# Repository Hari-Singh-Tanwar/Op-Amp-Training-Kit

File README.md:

View this project on [CADLAB.io](https://cadlab.io/project/29388). 

# Op-Amp-Training-Kit

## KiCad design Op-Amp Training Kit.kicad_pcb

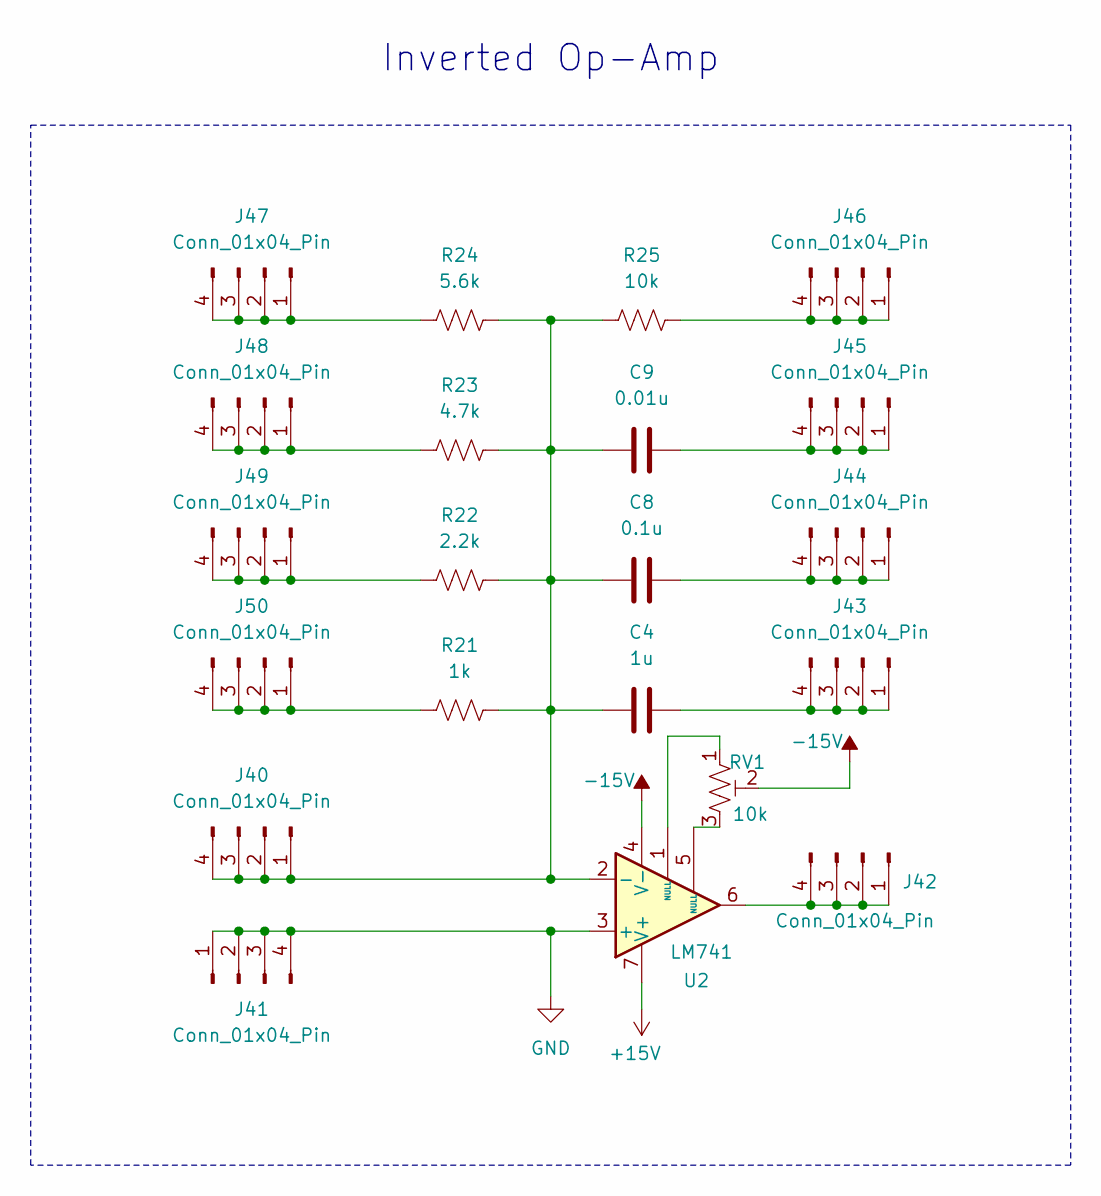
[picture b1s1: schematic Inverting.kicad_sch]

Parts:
C4: 1u; C_0805_2012Metric_Pad1.18x1.45mm_HandSolder
C8: 0.1u; C_0805_2012Metric_Pad1.18x1.45mm_HandSolder
C9: 0.01u; C_0805_2012Metric_Pad1.18x1.45mm_HandSolder
J40, J41, J42, J43, J44, J45, J46, J47, J48, J49, J50: Conn_01x04_Pin; PinHeader_1x04_P2.54mm_Vertical
R21: 1k; R_Axial_DIN0207_L6.3mm_D2.5mm_P10.16mm_Horizontal
R22: 2.2k; R_Axial_DIN0207_L6.3mm_D2.5mm_P10.16mm_Horizontal
R23: 4.7k; R_Axial_DIN0207_L6.3mm_D2.5mm_P10.16mm_Horizontal
R24: 5.6k; R_Axial_DIN0207_L6.3mm_D2.5mm_P10.16mm_Horizontal
R25: 10k; R_Axial_DIN0207_L6.3mm_D2.5mm_P10.16mm_Horizontal
RV1: 10k; Potentiometer_Bourns_3296W_Vertical
U2: LM741; DIP-8_W7.62mm_LongPads

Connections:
+15V: U2.7 (V+); also elsewhere on the board
-15V: RV1.2, U2.4 (V-); also elsewhere on the board
GND: J41.1, J41.2, J41.3, J41.4, U2.3 (+); also elsewhere on the board
unnamed: C4.1, C8.1, C9.1, J40.1, J40.2, J40.3, J40.4, R21.2, R22.2, R23.2, R24.2, R25.1, U2.2 (-)
unnamed: J42.1, J42.2, J42.3, J42.4, U2.6
unnamed: C4.2, J43.1, J43.2, J43.3, J43.4
unnamed: C8.2, J44.1, J44.2, J44.3, J44.4
unnamed: C9.2, J45.1, J45.2, J45.3, J45.4
unnamed: J46.1, J46.2, J46.3, J46.4, R25.2
unnamed: J47.1, J47.2, J47.3, J47.4, R24.1
unnamed: J48.1, J48.2, J48.3, J48.4, R23.1
unnamed: J49.1, J49.2, J49.3, J49.4, R22.1
unnamed: J50.1, J50.2, J50.3, J50.4, R21.1
unnamed: RV1.1, U2.1 (NULL)
unnamed: RV1.3, U2.5 (NULL)

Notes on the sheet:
Inverted Op-Amp

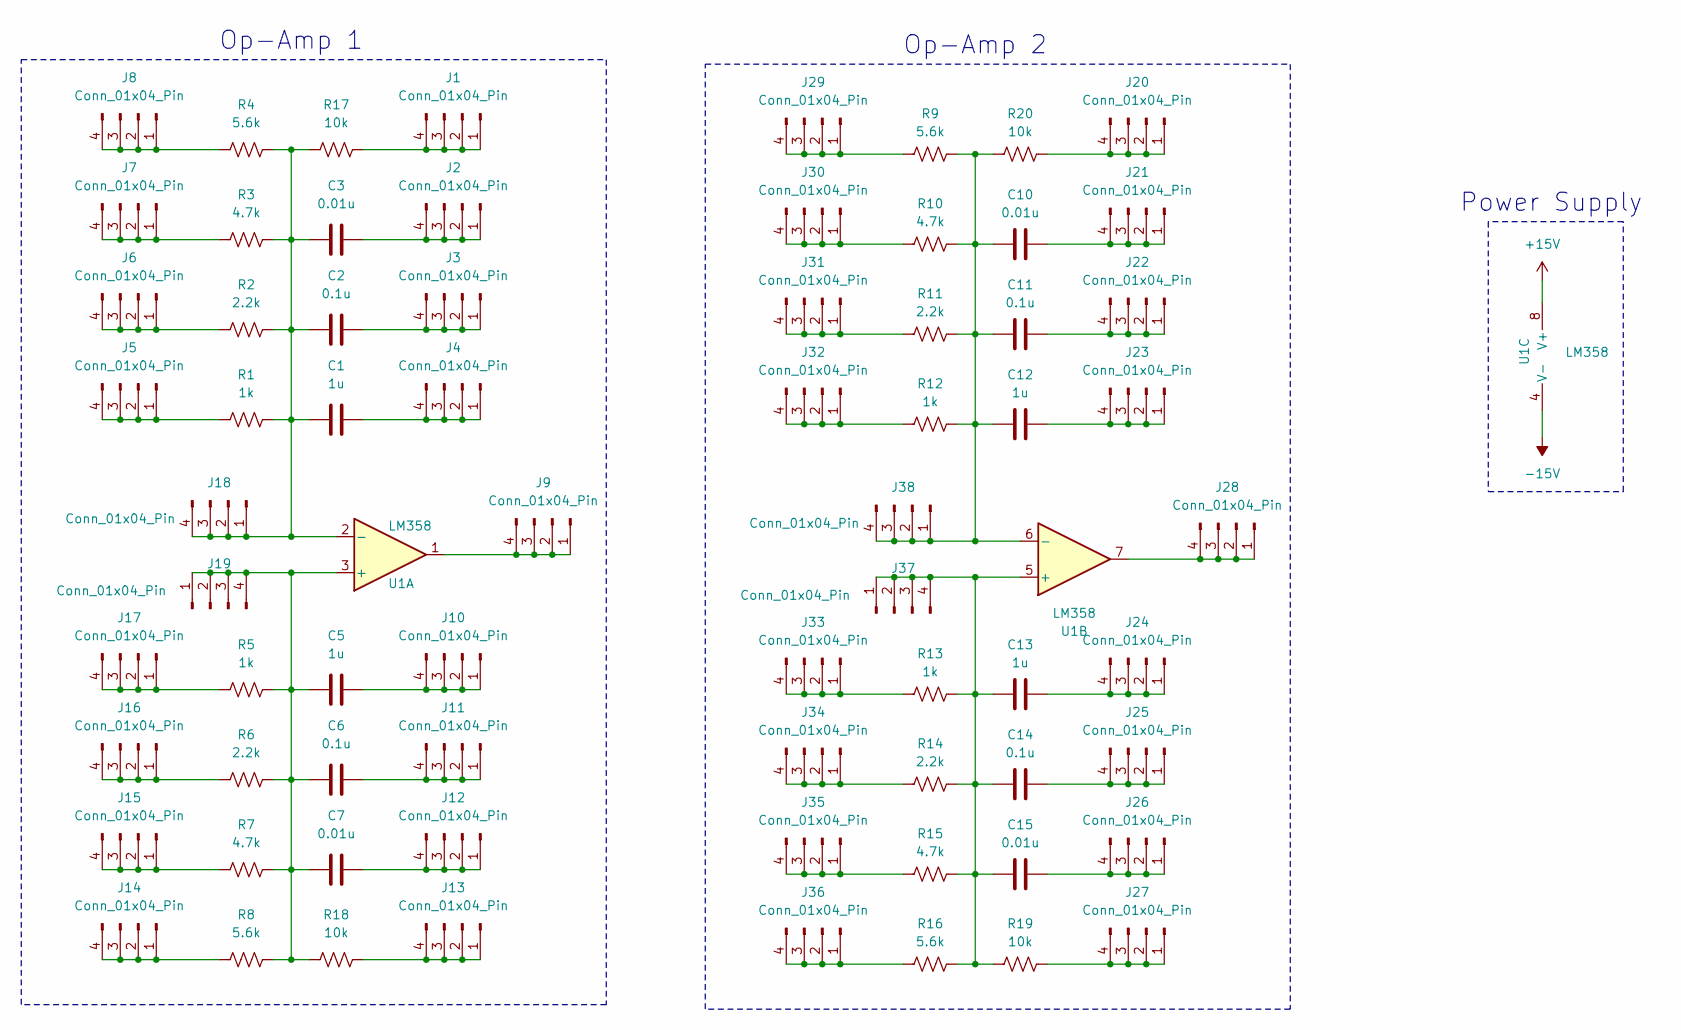
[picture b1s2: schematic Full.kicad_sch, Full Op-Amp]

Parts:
C1, C5, C12, C13: 1u; C_0805_2012Metric_Pad1.18x1.45mm_HandSolder
C2, C6, C11, C14: 0.1u; C_0805_2012Metric_Pad1.18x1.45mm_HandSolder
C3, C7, C10, C15: 0.01u; C_0805_2012Metric_Pad1.18x1.45mm_HandSolder
J1, J2, J3, J4, J5, J6, J7, J8, J9, J10, J11, J12, J13, J14, J15, J16, J17, J18, J19, J20, J21, J22, J23, J24, J25, J26, J27, J28, J29, J30, J31, J32, J33, J34, J35, J36, J37, J38: Conn_01x04_Pin; PinHeader_1x04_P2.54mm_Vertical
R1, R5, R12, R13: 1k; R_Axial_DIN0207_L6.3mm_D2.5mm_P10.16mm_Horizontal
R2, R6, R11, R14: 2.2k; R_Axial_DIN0207_L6.3mm_D2.5mm_P10.16mm_Horizontal
R3, R7, R10, R15: 4.7k; R_Axial_DIN0207_L6.3mm_D2.5mm_P10.16mm_Horizontal
R4, R8, R9, R16: 5.6k; R_Axial_DIN0207_L6.3mm_D2.5mm_P10.16mm_Horizontal
R17, R18, R19, R20: 10k; R_Axial_DIN0207_L6.3mm_D2.5mm_P10.16mm_Horizontal
U1: LM358; DIP-8_W7.62mm_LongPads

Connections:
+15V: U1.8 (V+); also elsewhere on the board
-15V: U1.4 (V-); also elsewhere on the board
unnamed: J1.1, J1.2, J1.3, J1.4, R17.2
unnamed: C3.2, J2.1, J2.2, J2.3, J2.4
unnamed: C2.2, J3.1, J3.2, J3.3, J3.4
unnamed: C1.2, J4.1, J4.2, J4.3, J4.4
unnamed: J5.1, J5.2, J5.3, J5.4, R1.1
unnamed: J6.1, J6.2, J6.3, J6.4, R2.1
unnamed: J7.1, J7.2, J7.3, J7.4, R3.1
unnamed: J8.1, J8.2, J8.3, J8.4, R4.1
unnamed: J9.1, J9.2, J9.3, J9.4, U1.1
unnamed: C5.2, J10.1, J10.2, J10.3, J10.4
unnamed: C6.2, J11.1, J11.2, J11.3, J11.4
unnamed: C7.2, J12.1, J12.2, J12.3, J12.4
unnamed: J13.1, J13.2, J13.3, J13.4, R18.2
unnamed: J14.1, J14.2, J14.3, J14.4, R8.1
unnamed: J15.1, J15.2, J15.3, J15.4, R7.1
unnamed: J16.1, J16.2, J16.3, J16.4, R6.1
unnamed: J17.1, J17.2, J17.3, J17.4, R5.1
unnamed: C1.1, C2.1, C3.1, J18.1, J18.2, J18.3, J18.4, R1.2, R2.2, R3.2, R4.2, R17.1, U1.2 (-)
unnamed: C5.1, C6.1, C7.1, J19.1, J19.2, J19.3, J19.4, R5.2, R6.2, R7.2, R8.2, R18.1, U1.3 (+)
unnamed: J20.1, J20.2, J20.3, J20.4, R20.2
unnamed: C10.2, J21.1, J21.2, J21.3, J21.4
unnamed: C11.2, J22.1, J22.2, J22.3, J22.4
unnamed: C12.2, J23.1, J23.2, J23.3, J23.4
unnamed: C13.2, J24.1, J24.2, J24.3, J24.4
unnamed: C14.2, J25.1, J25.2, J25.3, J25.4
unnamed: C15.2, J26.1, J26.2, J26.3, J26.4
unnamed: J27.1, J27.2, J27.3, J27.4, R19.2
unnamed: J28.1, J28.2, J28.3, J28.4, U1.7
unnamed: J29.1, J29.2, J29.3, J29.4, R9.1
unnamed: J30.1, J30.2, J30.3, J30.4, R10.1
unnamed: J31.1, J31.2, J31.3, J31.4, R11.1
unnamed: J32.1, J32.2, J32.3, J32.4, R12.1
unnamed: J33.1, J33.2, J33.3, J33.4, R13.1
unnamed: J34.1, J34.2, J34.3, J34.4, R14.1
unnamed: J35.1, J35.2, J35.3, J35.4, R15.1
unnamed: J36.1, J36.2, J36.3, J36.4, R16.1
unnamed: C13.1, C14.1, C15.1, J37.1, J37.2, J37.3, J37.4, R13.2, R14.2, R15.2, R16.2, R19.1, U1.5 (+)
unnamed: C10.1, C11.1, C12.1, J38.1, J38.2, J38.3, J38.4, R9.2, R10.2, R11.2, R12.2, R20.1, U1.6 (-)

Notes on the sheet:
Power Supply
Op-Amp 1
Op-Amp 2

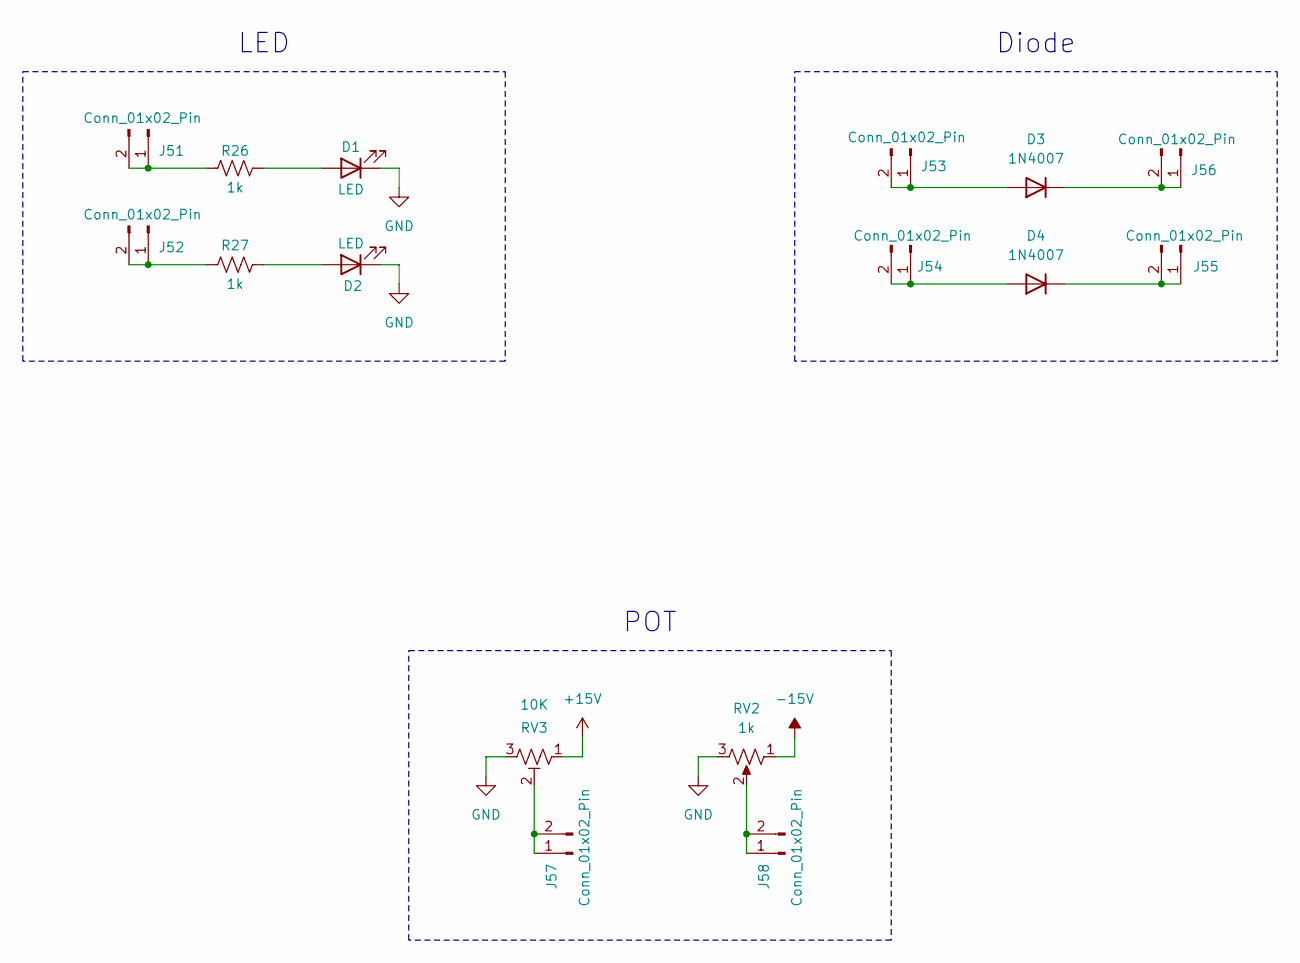
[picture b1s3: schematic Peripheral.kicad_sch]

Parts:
D1: LED; LED_D5.0mm
D2: LED; LED_D5.0mm_Clear
D3, D4: 1N4007; D_DO-41_SOD81_P10.16mm_Horizontal
J51, J52, J53, J54, J55, J56, J57, J58: Conn_01x02_Pin; PinHeader_1x02_P2.54mm_Vertical
R26, R27: 1k; R_Axial_DIN0207_L6.3mm_D2.5mm_P10.16mm_Horizontal
RV2: 1k; Potentiometer_Runtron_RM-065_Vertical
RV3: 10K; Potentiometer_Runtron_RM-065_Vertical

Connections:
+15V: RV3.1; also elsewhere on the board
-15V: RV2.1; also elsewhere on the board
GND: D1.1 (K), D2.1 (K), RV2.3, RV3.3; also elsewhere on the board
unnamed: D1.2 (A), R26.2
unnamed: D2.2 (A), R27.2
unnamed: D3.2 (A), J53.1, J53.2
unnamed: D3.1 (K), J56.1, J56.2
unnamed: D4.2 (A), J54.1, J54.2
unnamed: D4.1 (K), J55.1, J55.2
unnamed: J51.1, J51.2, R26.1
unnamed: J52.1, J52.2, R27.1
unnamed: J57.1, J57.2, RV3.2
unnamed: J58.1, J58.2, RV2.2

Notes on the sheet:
Diode
POT
LED

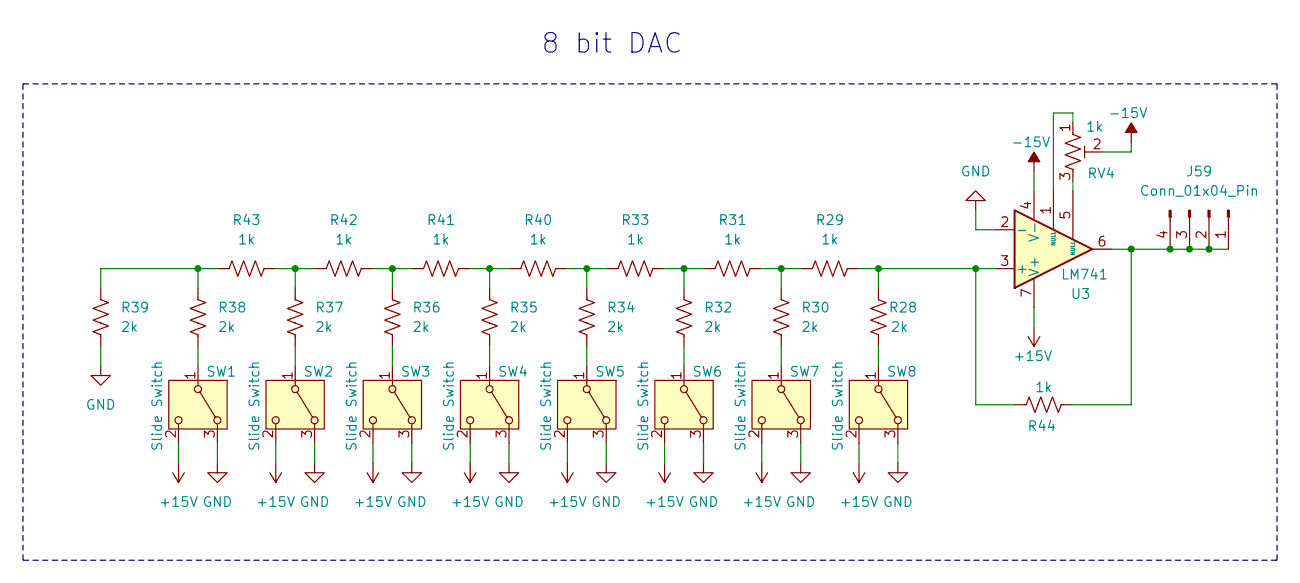
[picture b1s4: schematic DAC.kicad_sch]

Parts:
J59: Conn_01x04_Pin; PinHeader_1x04_P2.54mm_Vertical
R28, R30, R32, R34, R35, R36, R37, R38, R39: 2k; R_0805_2012Metric_Pad1.20x1.40mm_HandSolder
R29, R31, R33, R40, R41, R42, R43, R44: 1k; R_0805_2012Metric_Pad1.20x1.40mm_HandSolder
RV4: 1k; Potentiometer_Bourns_3296W_Vertical
SW1, SW2, SW3, SW4, SW5, SW6, SW7, SW8: Slide Switch; SW_Slide-03_Wuerth-WS-SLTV_10x2.5x6.4_P2.54mm
U3: LM741; DIP-8_W7.62mm_LongPads

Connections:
+15V: SW1.2 (C), SW2.2 (C), SW3.2 (C), SW4.2 (C), SW5.2 (C), SW6.2 (C), SW7.2 (C), SW8.2 (C), U3.7 (V+); also elsewhere on the board
-15V: RV4.2, U3.4 (V-); also elsewhere on the board
GND: R39.2, SW1.3 (A), SW2.3 (A), SW3.3 (A), SW4.3 (A), SW5.3 (A), SW6.3 (A), SW7.3 (A), SW8.3 (A), U3.2 (-); also elsewhere on the board
unnamed: J59.1, J59.2, J59.3, J59.4, R44.1, U3.6
unnamed: R29.2, R30.1, R31.1
unnamed: R31.2, R32.1, R33.1
unnamed: R33.2, R34.1, R40.1
unnamed: R35.1, R40.2, R41.1
unnamed: R36.1, R41.2, R42.1
unnamed: R37.1, R42.2, R43.1
unnamed: R38.1, R39.1, R43.2
unnamed: RV4.1, U3.1 (NULL)
unnamed: RV4.3, U3.5 (NULL)
unnamed: R38.2, SW1.1 (B)
unnamed: R37.2, SW2.1 (B)
unnamed: R36.2, SW3.1 (B)
unnamed: R35.2, SW4.1 (B)
unnamed: R34.2, SW5.1 (B)
unnamed: R32.2, SW6.1 (B)
unnamed: R30.2, SW7.1 (B)
unnamed: R28.2, SW8.1 (B)
unnamed: R28.1, R29.1, R44.2, U3.3 (+)

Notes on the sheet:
8 bit DAC

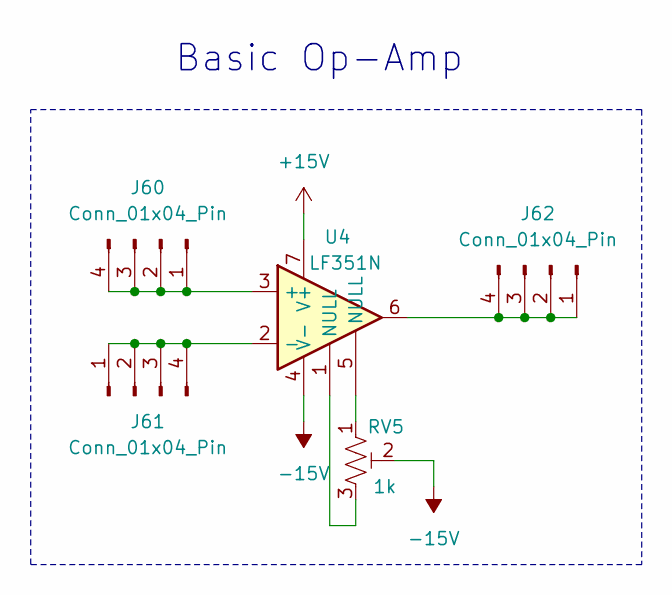
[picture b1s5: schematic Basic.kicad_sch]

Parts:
J60, J61, J62: Conn_01x04_Pin; PinHeader_1x04_P2.54mm_Vertical
RV5: 1k; Potentiometer_Bourns_3296W_Vertical
U4: LF351N; DIP-8_W7.62mm_LongPads

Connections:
+15V: U4.7 (V+); also elsewhere on the board
-15V: RV5.2, U4.4 (V-); also elsewhere on the board
unnamed: J60.1, J60.2, J60.3, J60.4, U4.3 (+)
unnamed: J61.1, J61.2, J61.3, J61.4, U4.2 (-)
unnamed: J62.1, J62.2, J62.3, J62.4, U4.6
unnamed: RV5.1, U4.5 (NULL)
unnamed: RV5.3, U4.1 (NULL)

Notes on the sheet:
Basic Op-Amp

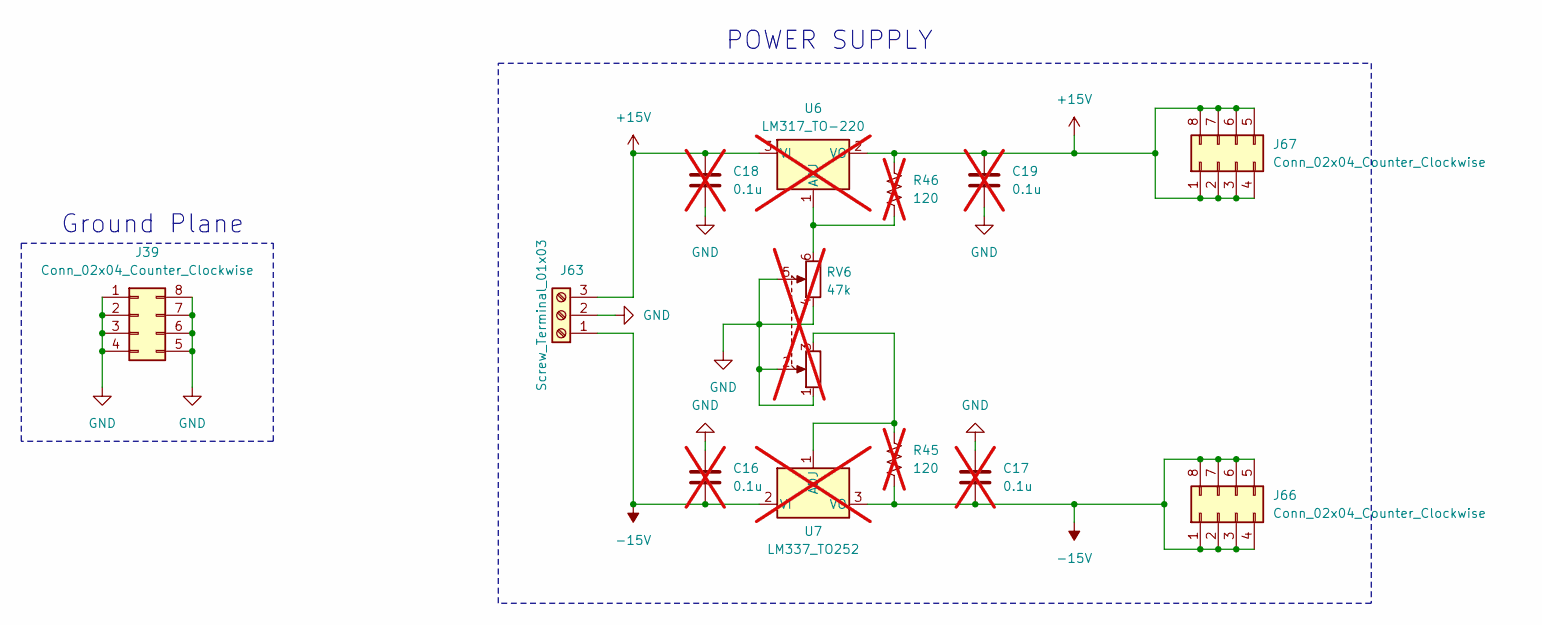
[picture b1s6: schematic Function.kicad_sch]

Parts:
C16, C17, C18, C19: 0.1u; C_Disc_D4.7mm_W2.5mm_P5.00mm; not fitted
J39, J66, J67: Conn_02x04_Counter_Clockwise; PinHeader_2x04_P2.54mm_Vertical
J63: Screw_Terminal_01x03; TerminalBlock_Phoenix_PT-1,5-3-5.0-H_1x03_P5.00mm_Horizontal
R45, R46: 120; R_Axial_DIN0207_L6.3mm_D2.5mm_P10.16mm_Horizontal; not fitted
RV6: 47k; Potentiometer_Alps_RK163_Dual_Horizontal; not fitted
U6: LM317_TO-220; TO-220-3_Vertical; not fitted
U7: LM337_TO252; TO-252-2; not fitted

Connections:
+15V: C18.1, C19.1, J63.3, J67.1, J67.2, J67.3, J67.4, J67.5, J67.6, J67.7, J67.8, R46.1, U6.2 (VO), U6.3 (VI); also elsewhere on the board
-15V: C16.2, C17.2, J63.1, J66.1, J66.2, J66.3, J66.4, J66.5, J66.6, J66.7, J66.8, R45.2, U7.2 (VI), U7.3 (VO); also elsewhere on the board
GND: C16.1, C17.1, C18.2, C19.2, J39.1, J39.2, J39.3, J39.4, J39.5, J39.6, J39.7, J39.8, J63.2, RV6.1, RV6.2, RV6.4, RV6.5; also elsewhere on the board
unnamed: R45.1, RV6.3, U7.1 (ADJ)
unnamed: R46.2, RV6.6, U6.1 (ADJ)

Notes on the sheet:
Ground Plane
POWER SUPPLY

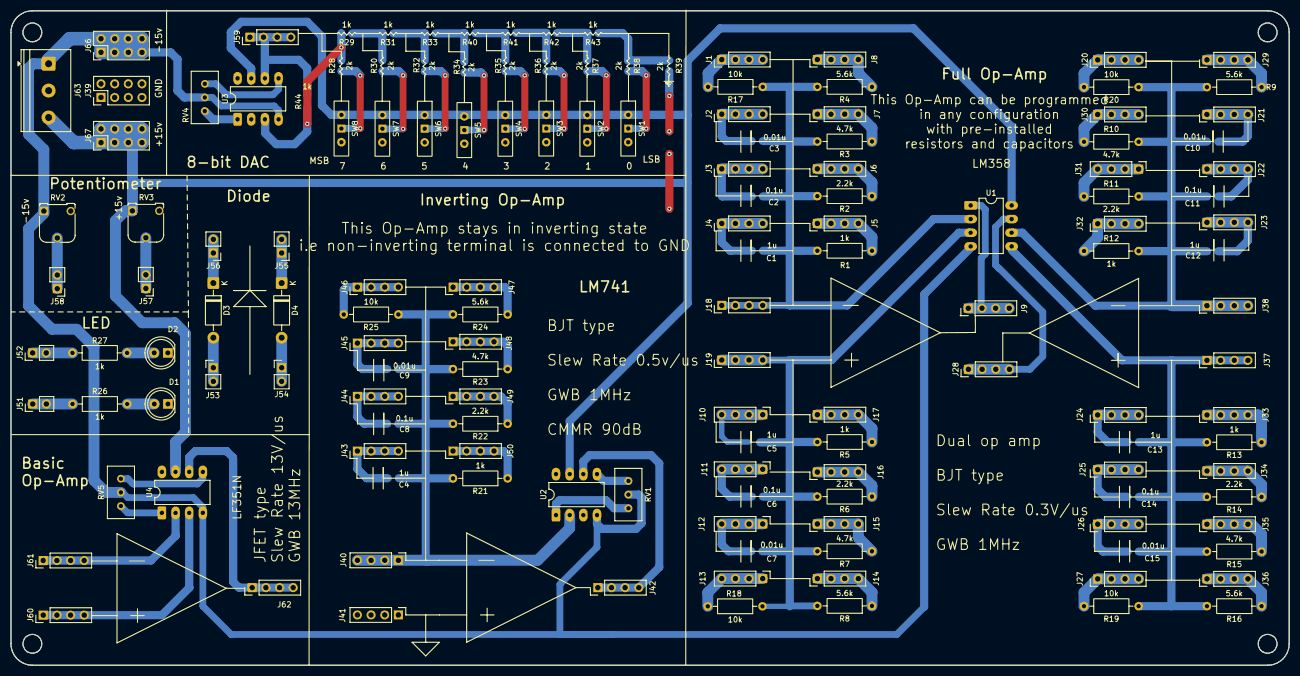
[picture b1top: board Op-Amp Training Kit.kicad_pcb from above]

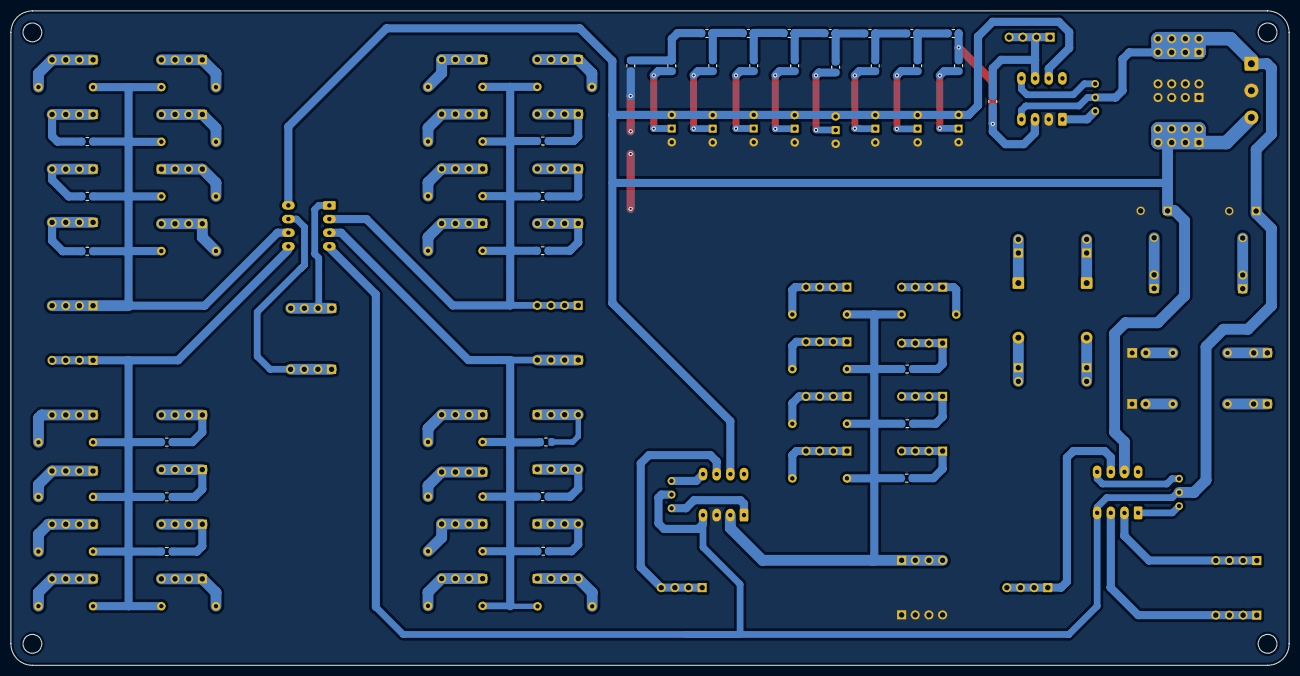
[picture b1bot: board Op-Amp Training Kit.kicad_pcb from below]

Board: 2 copper layers, 237.7 x 121.7 mm, 145 parts (32 on the bottom side), 87 nets.

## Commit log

2025-05-21 Made all the schematics
2025-05-21 Backlink to CADLAB.io has been added.
2025-05-22 made Full Op-Amp
2025-05-22 added inverting ckt
2025-05-23 Edited DAC
2025-06-02 Added fetures
2025-06-03 Power Supply
2025-06-05 Floor Planning 50%
2025-06-06 Completed V1
2025-06-06 Updated track
2025-06-10 Filanl Pakka
2025-06-10 pakka Final 2.0
2025-06-11 Changes in Silkscreen
